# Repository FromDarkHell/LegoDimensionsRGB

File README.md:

## LegoDimensionsRGB

This project is a reverse-engineered implementation of a LEGO Dimensions (currently *only* PS3 / Wii U) playpad.  
This project also includes a simpler project which communicates with an OEM playpad to act as a lamp/night-light, as well as a Python script for communication as well.

### Project Layout
Inside of `projects`, you can see a few different sub-projects which each have their own purpose.

- [basic-emulator](/projects/basic-emulator/) is an implementation of the playpad HID spec, running on a Raspberry Pi Pico W, alongside a Web UI for easy controls.
- [rgb-controller](/projects/rgb-controller/) is a simpler project which sends basic USB HID commands *to* an existing, stock playpad for use as a lamp. This is powered by an ESP32-S3, and comes with a simple Web UI for controlling colors.

### Credits

A large portion of the emulator project is based on [AlinaNova21/node-ld](https://github.com/AlinaNova21/node-ld/tree/master), as well as [Berny23/LD-Toypad-Emulator](https://github.com/Berny23/LD-ToyPad-Emulator).

The Python tools is predominantly based on [woodenphone/lego_dimensions_protocol](https://github.com/woodenphone/lego_dimensions_protocol/blob/master/lego_dimensions_gateway.py). The main difference is that I have updated it to support Python 3 as well as added a `connected()` status function to determine if the playpad was disconnected.

### Support

If you for some reason want to support me financially for this project (or others I make), you can donate to me via [ko-fi](https://ko-fi.com/fromdarkhell) or [Patreon](https://patreon.com/fromdarkhell).

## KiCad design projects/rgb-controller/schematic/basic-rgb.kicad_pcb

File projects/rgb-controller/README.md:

## rgb-controller

This project is a simple ESP32-S3-based controller for (PS3/Wii U/PS4) LEGO Dimensions playpads.  
Note: **This project does not emulate a full playpad. It only provides remote control of the LED colors via a web interface.**

### Features

- Control the colors via a basic HTML webpage
- (Semi) real-time HTTP logs of USB packets / etc

### Hardware
- ESP32-S3 (i.e. [Seeed Studio XIAO ESP32-S3](https://wiki.seeedstudio.com/xiao_esp32s3_getting_started/))
- USB 2.0 Breakout Board ([Example](https://www.amazon.com/dp/B07W7XMV3W))

How To:
- Connect the USB breakout board D-/D+ pins to your ESP32  
- Splice a USB cable (or use a USB C/etc breakout board), and connect the VUSB and GND to the ESP32 *and* the USB Breakout Board.  

Additionally, this repo also includes a basic schematic & PCB which you can use as a guide, or as an easy to use wiring setup. Enjoy!  

### Usage

1. Flash the firmware onto your ESP32-S3
2. Wire your ESP32-S3 (see above)
3. Connect your ESP32-S3 to your power source
4. It will create a WiFi AP you can connect to named, `captive`.
    - Connect to `captive`, and then enter your WiFi credentials.
5. Wait for the reboot, and connect to your WiFi network.
6. Then you can access the playpad via `playpad.local` (via MDNS)
7. Start changing colors!

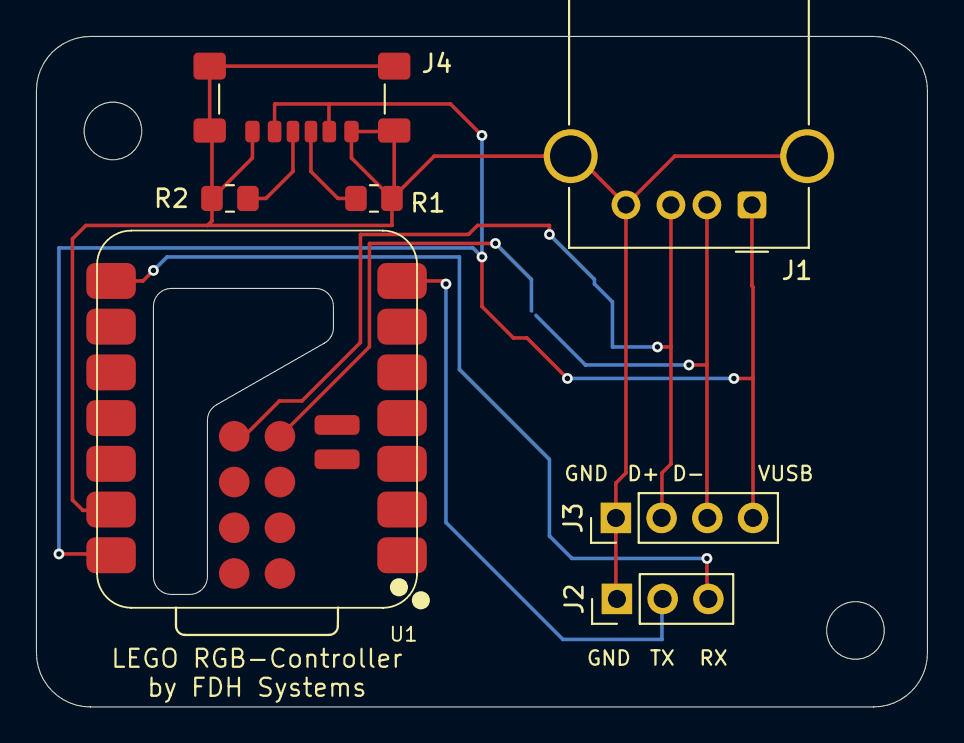
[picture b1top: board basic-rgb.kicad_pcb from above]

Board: 2 copper layers, 49.5 x 37.2 mm, 7 parts (0 on the bottom side), 8 nets.

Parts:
J1: PLAYPAD; USB_A_Molex_67643_Horizontal
J2: FTDI; PinHeader_1x03_P2.54mm_Vertical
J3: USB_DBG; PinHeader_1x04_P2.54mm_Vertical
J4: USB_C_Receptacle_PowerOnly_6P; USB_C_Receptacle_GCT_USB4135-GF-A_6P_TopMnt_Horizontal
R1, R2: 5.1k; R_0805_2012Metric_Pad1.20x1.40mm_HandSolder
U1: XIAO-ESP32-S3-SMD; XIAO-ESP32S3-SMD

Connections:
+5V: J1.1 (VBUS), J3.4, J4.A9 (VBUS), J4.B9 (VBUS), U1.14 (5V)
GND: J1.4 (GND), J1.SH, J2.1, J3.1, J4.A12 (GND), J4.B12 (GND), J4.SH, R1.2, R2.2, U1.13 (GND)
unnamed: J1.3 (D+), J3.2, U1.24 (USB_DP)
unnamed: J1.2 (D-), J3.3, U1.23 (USB_DN)
unnamed: J2.2, U1.7 (GPIO43_A6_D6_TX)
unnamed: J2.3, U1.8 (GPIO44_D7_RX)
unnamed: J4.A5 (CC1), R1.1
unnamed: J4.B5 (CC2), R2.1

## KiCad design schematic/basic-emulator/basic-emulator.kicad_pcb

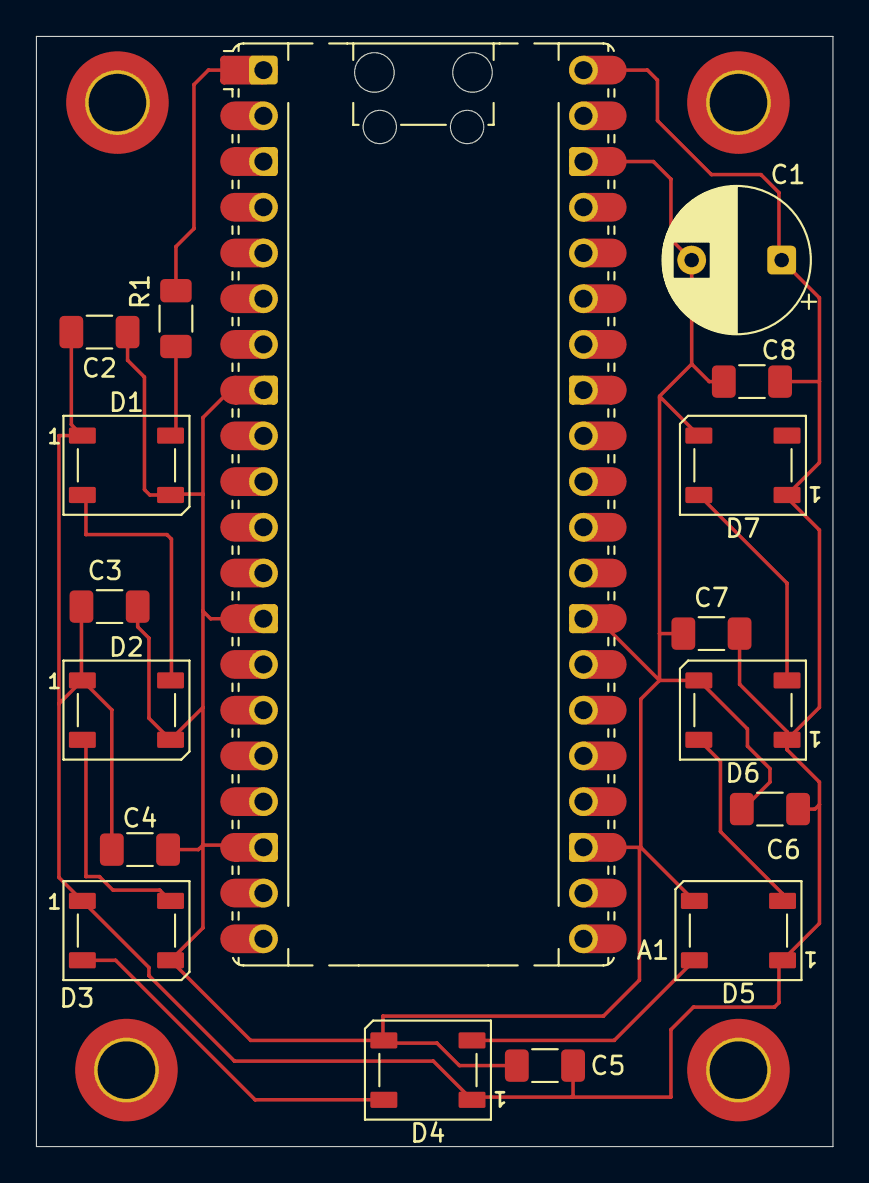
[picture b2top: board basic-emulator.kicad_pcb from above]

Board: 2 copper layers, 44.2 x 61.7 mm, 17 parts (0 on the bottom side), 10 nets.

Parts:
A1: RaspberryPi_Pico_W; RaspberryPi_Pico_Common_Unspecified
C1: 500µf, 16V; CP_Radial_D8.0mm_P5.00mm
C2, C3, C4, C5, C6, C7, C8: 104; C_1206_3216Metric_Pad1.33x1.80mm_HandSolder
D1, D2, D3, D4, D5, D6, D7: WS2812B; LED_WS2812B_PLCC4_5.0x5.0mm_P3.2mm
R1: 400Ω; R_1206_3216Metric_Pad1.30x1.75mm_HandSolder

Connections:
+5V: A1.40 (VBUS), C1.1, C2.1, C3.1, C4.1, C5.1, C6.1, C7.1, C8.1, D1.1 (VDD), D2.1 (VDD), D3.1 (VDD), D4.1 (VDD), D5.1 (VDD), D6.1 (VDD), D7.1 (VDD)
GND: A1.3 (GND), A1.8 (GND), A1.13 (GND), A1.18 (GND), A1.23 (GND), A1.28 (GND), A1.33 (AGND), A1.38 (GND), C1.2, C2.2, C3.2, C4.2, C5.2, C6.2, C7.2, C8.2, D1.3 (VSS), D2.3 (VSS), D3.3 (VSS), D4.3 (VSS), D5.3 (VSS), D6.3 (VSS), D7.3 (VSS)
unnamed: A1.1 (GPIO0), R1.2
unnamed: D1.4 (DIN), R1.1
unnamed: D1.2 (DOUT), D2.4 (DIN)
unnamed: D2.2 (DOUT), D3.4 (DIN)
unnamed: D3.2 (DOUT), D4.4 (DIN)
unnamed: D4.2 (DOUT), D5.4 (DIN)
unnamed: D5.2 (DOUT), D6.4 (DIN)
unnamed: D6.2 (DOUT), D7.4 (DIN)

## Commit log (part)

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2025-06-22 Fix Static Coloring
2025-08-14 Initial basic-rgb commit
2026-03-06 Very basic basic-emulator implementation + PCB
2026-03-11 Fix formatting + PS3 HID Bugs (Needs extra fix later, implemented into Adafruit TinyUSB)
2026-03-12 Add websockets support for colors + extra packets
2026-03-13 Restructure Repository
2026-03-16 Extra bug fixes, more memory allocation fixes, fix packet parsing
2026-03-16 Update READMEs
2026-03-26 feat: updates emu for websocket toybox-level updates
2026-05-07 feat: add xbox 360 support + extra emulator tweaks
    Adds Xbox 360 Support into the RGB-Controller project, tweaks fronend UI design for emulator, as well as adding a case for the RGB-Controller + Redesigning the PCB for RGB-controller
    BREAKING CHANGE:
2026-05-18 refactor(Basic-Emulator): rename playpad to toypad in cpp
2026-06-18 feat(usb): add x360 usbdsec authentication
    Supports modded Xbox 360s with the usbdsec patch applied
